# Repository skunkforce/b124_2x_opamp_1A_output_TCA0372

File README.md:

# edgy_board number b124
This design is part of the [edgy board project](https://github.com/skunkforce/edgy_boards).

# getting started
This repository uses submodules. After cloning use the command 

```$ git submodule update --init --recursive```

to pull the submodules before opening the project with kicad. 

# Tests
Tests can be found in [TESTS.md](TESTS.md)

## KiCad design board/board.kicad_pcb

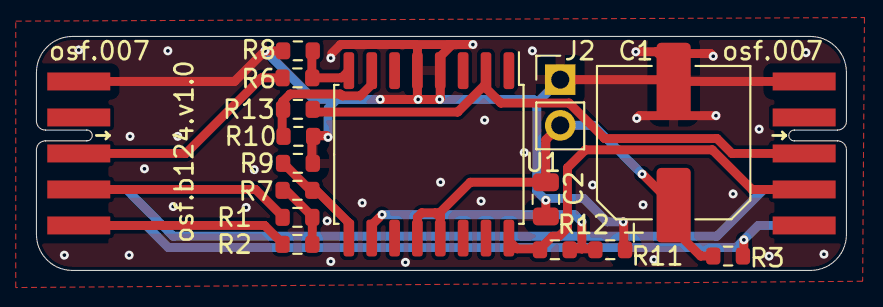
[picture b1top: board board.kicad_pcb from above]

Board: 2 copper layers, 45.0 x 13.0 mm, 18 parts (1 on the bottom side), 14 nets.

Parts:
C1: 100uF; CP_Elec_8x6.9
C2: 1uF; C_0805_2012Metric
J1: 007_ADC; on_edge_2x05_device
J2: Conn_01x02_Male; PinHeader_1x02_P2.54mm_Vertical
J3: 007_ADC; on_edge_2x05_host
LOGO1: Logo_Open_Hardware_Small; OSHW-Symbol_6.7x6mm_SilkScreen
R1, R2, R3, R6, R7, R12, R13: 0R; R_0603_1608Metric
R8, R9, R10, R11: d.n.p; R_0603_1608Metric
U1: TCA0372; SOIC-16W_7.5x10.3mm_P1.27mm

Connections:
/VDD: C1.1, C2.1, J2.2, R3.2, U1.12 (V+), U1.13 (V+)
/amp/in1: J1.3 (ADC0), R6.2
/amp/in2: R1.2, R2.2, R7.2
/amp/out1: J3.3 (ADC0), R13.1, U1.2
/amp/out2: J3.4 (ADC1), R12.1, U1.16
GND: C1.2, C2.2, J1.1 (GND), J2.1, J3.1 (GND), R8.1, R9.1, R10.1, R11.1, U1.4 (V-), U1.5 (V-)
unnamed: J1.4 (ADC1), R1.1
unnamed: J1.5 (ADC2), R2.1
unnamed: J1.9 (3.3V), J3.9 (3.3V)
unnamed: J1.10 (5V), J3.10 (5V), R3.1
unnamed: R6.1, R8.2, U1.8 (+)
unnamed: R7.1, R9.2, U1.9 (+)
unnamed: R10.2, R13.2, U1.7 (-)
unnamed: R11.2, R12.2, U1.10 (-)

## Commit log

2023-04-13 initial
2023-05-10 added missing schemetic
